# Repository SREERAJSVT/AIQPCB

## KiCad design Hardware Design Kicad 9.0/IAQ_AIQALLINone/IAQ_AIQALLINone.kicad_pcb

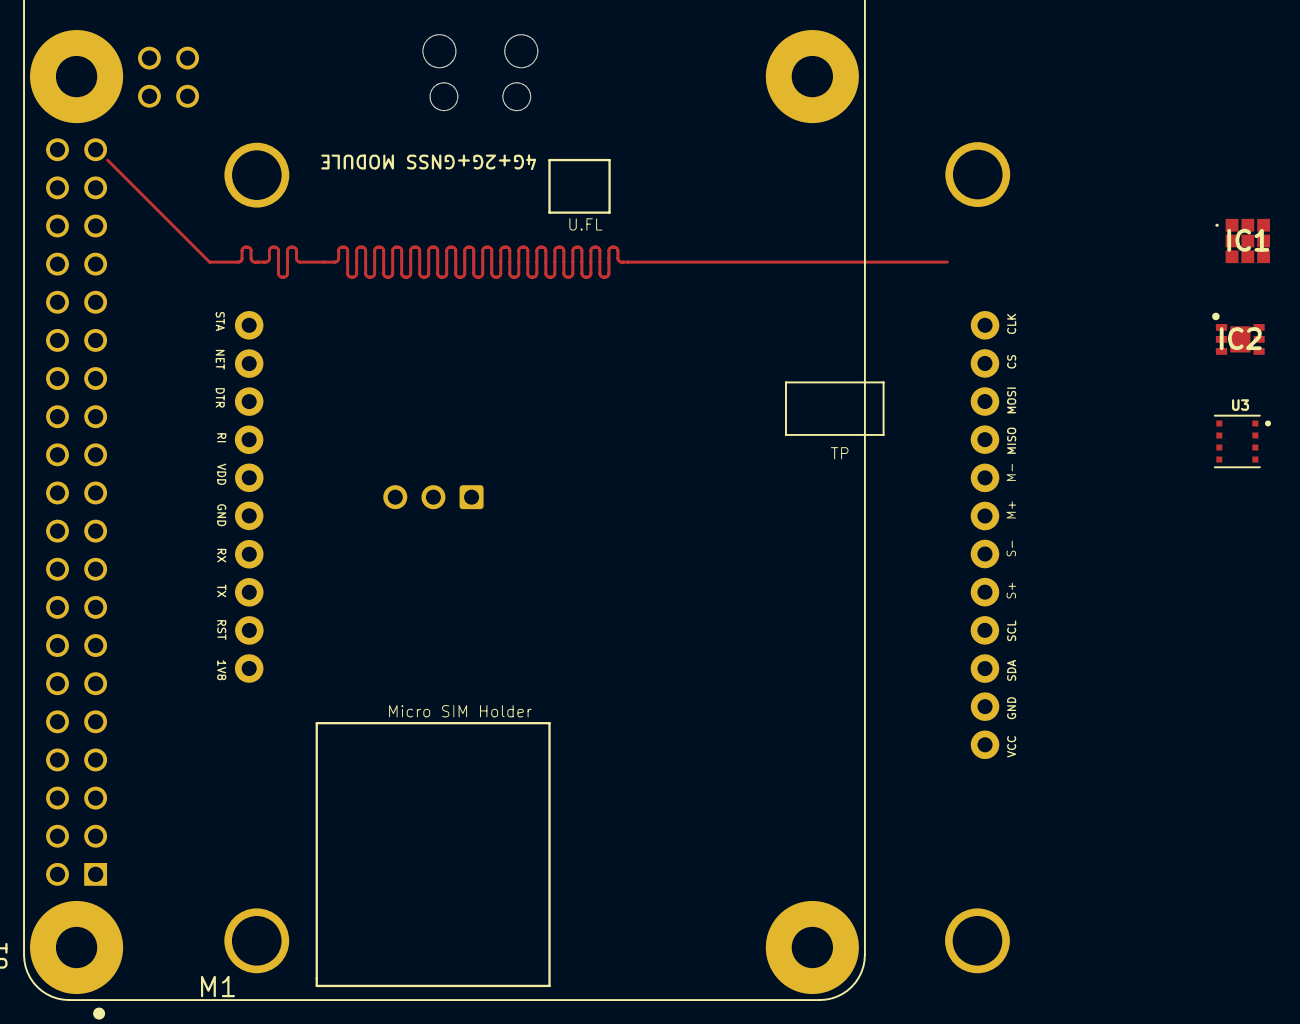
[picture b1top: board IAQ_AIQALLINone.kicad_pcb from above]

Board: 2 copper layers, 6 parts (1 on the bottom side), 5 nets.

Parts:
IC1: ENS160-BGLT; ENS160BGLT
IC2: SGP41-D-R4; SON80P244X244X95-7N
M1: A7670C&72S
U1: RASPBERRY_PI_4B_4GB; MODULE_RASPBERRY_PI_4B_4GB
U2: RASPBERRY_PI_PICO_W; RaspberryPi_Pico_W_SMD_HandSolder
U3: BME688; IC_BME688

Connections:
3V3: U1.1 (3V3), U1.17 (3V3)
5V: U1.2 (5V), U1.4 (5V)
GND: U1.6 (GND), U1.9 (GND), U1.14 (GND), U1.20 (GND), U1.25 (GND), U1.30 (GND), U1.34 (GND), U1.39 (GND), U2.3 (GND), U2.8 (GND), U2.13 (GND), U2.18 (GND), U2.23 (GND), U2.28 (GND), U2.38 (GND), U3.1 (GND), U3.7 (GND)
unnamed: M1.GND, M1.P$25 (GND), M1.P$26 (GND), M1.P$27 (GND), M1.P$28 (GND)
SHIELD: U1.S1 (SHIELD), U1.S2 (SHIELD), U1.S3 (SHIELD), U1.S4 (SHIELD)

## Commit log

2026-03-19 19032026
    PCB Design March
2026-03-19 update
    141619032026
